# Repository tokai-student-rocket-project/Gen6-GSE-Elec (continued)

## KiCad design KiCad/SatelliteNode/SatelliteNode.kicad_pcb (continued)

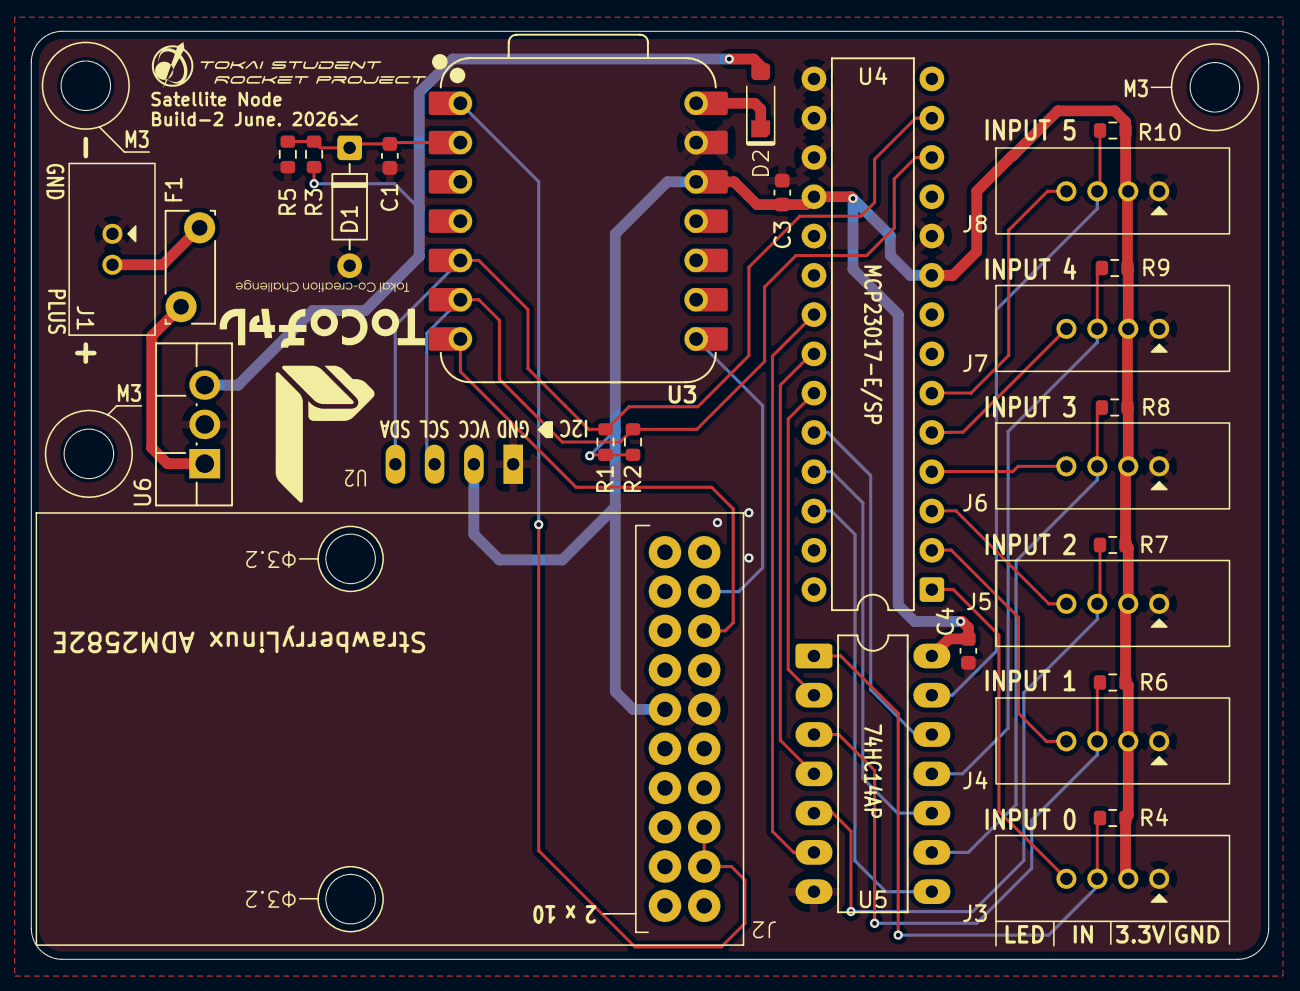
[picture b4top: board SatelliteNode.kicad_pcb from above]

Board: 2 copper layers, 80.0 x 60.0 mm, 32 parts (0 on the bottom side), 30 nets.

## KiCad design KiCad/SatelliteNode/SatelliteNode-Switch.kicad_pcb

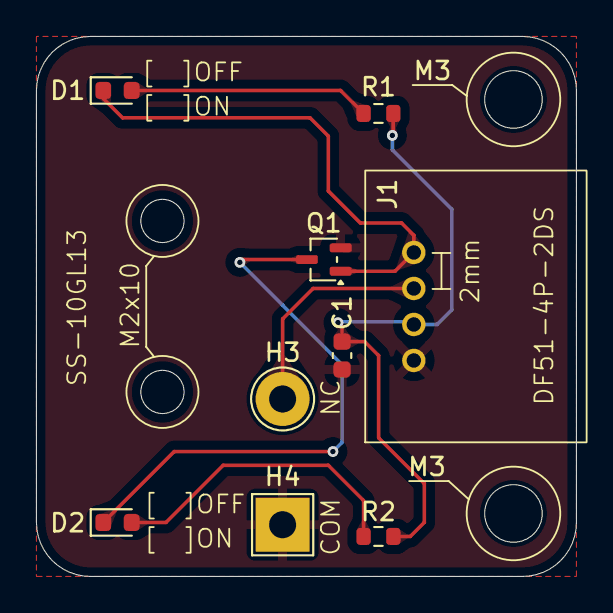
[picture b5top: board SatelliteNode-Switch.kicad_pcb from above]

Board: 2 copper layers, 30.0 x 30.0 mm, 11 parts (0 on the bottom side), 7 nets.

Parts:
C1: 0.1uF; C_0603_1608Metric
D1: GREEN; LED_0603_1608Metric
D2: RED; LED_0603_1608Metric
H3: MountingHole_Pad; TestPoint_THTPad_D3.0mm_Drill1.5mm
H4: MountingHole_Pad; TestPoint_THTPad_3.0x3.0mm_Drill1.5mm
J1: DF51A-4P-2DS
M3, M3#2: MountingHole; MountingHole_3.2mm_M3
Q1: DTC123EU3; SOT-323_SC-70
R1, R2: 330R; R_0603_1608Metric

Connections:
+3.3V: C1.1, J1.2, R1.1, R2.1
GND: C1.2, H4.1, J1.1, Q1.2 (E)
LED_CTRL: D1.1 (K), J1.4, Q1.1 (B)
unnamed: D1.2 (A), R1.2
unnamed: D2.2 (A), R2.2
unnamed: D2.1 (K), Q1.3 (C)
SW_OUT: H3.1, J1.3

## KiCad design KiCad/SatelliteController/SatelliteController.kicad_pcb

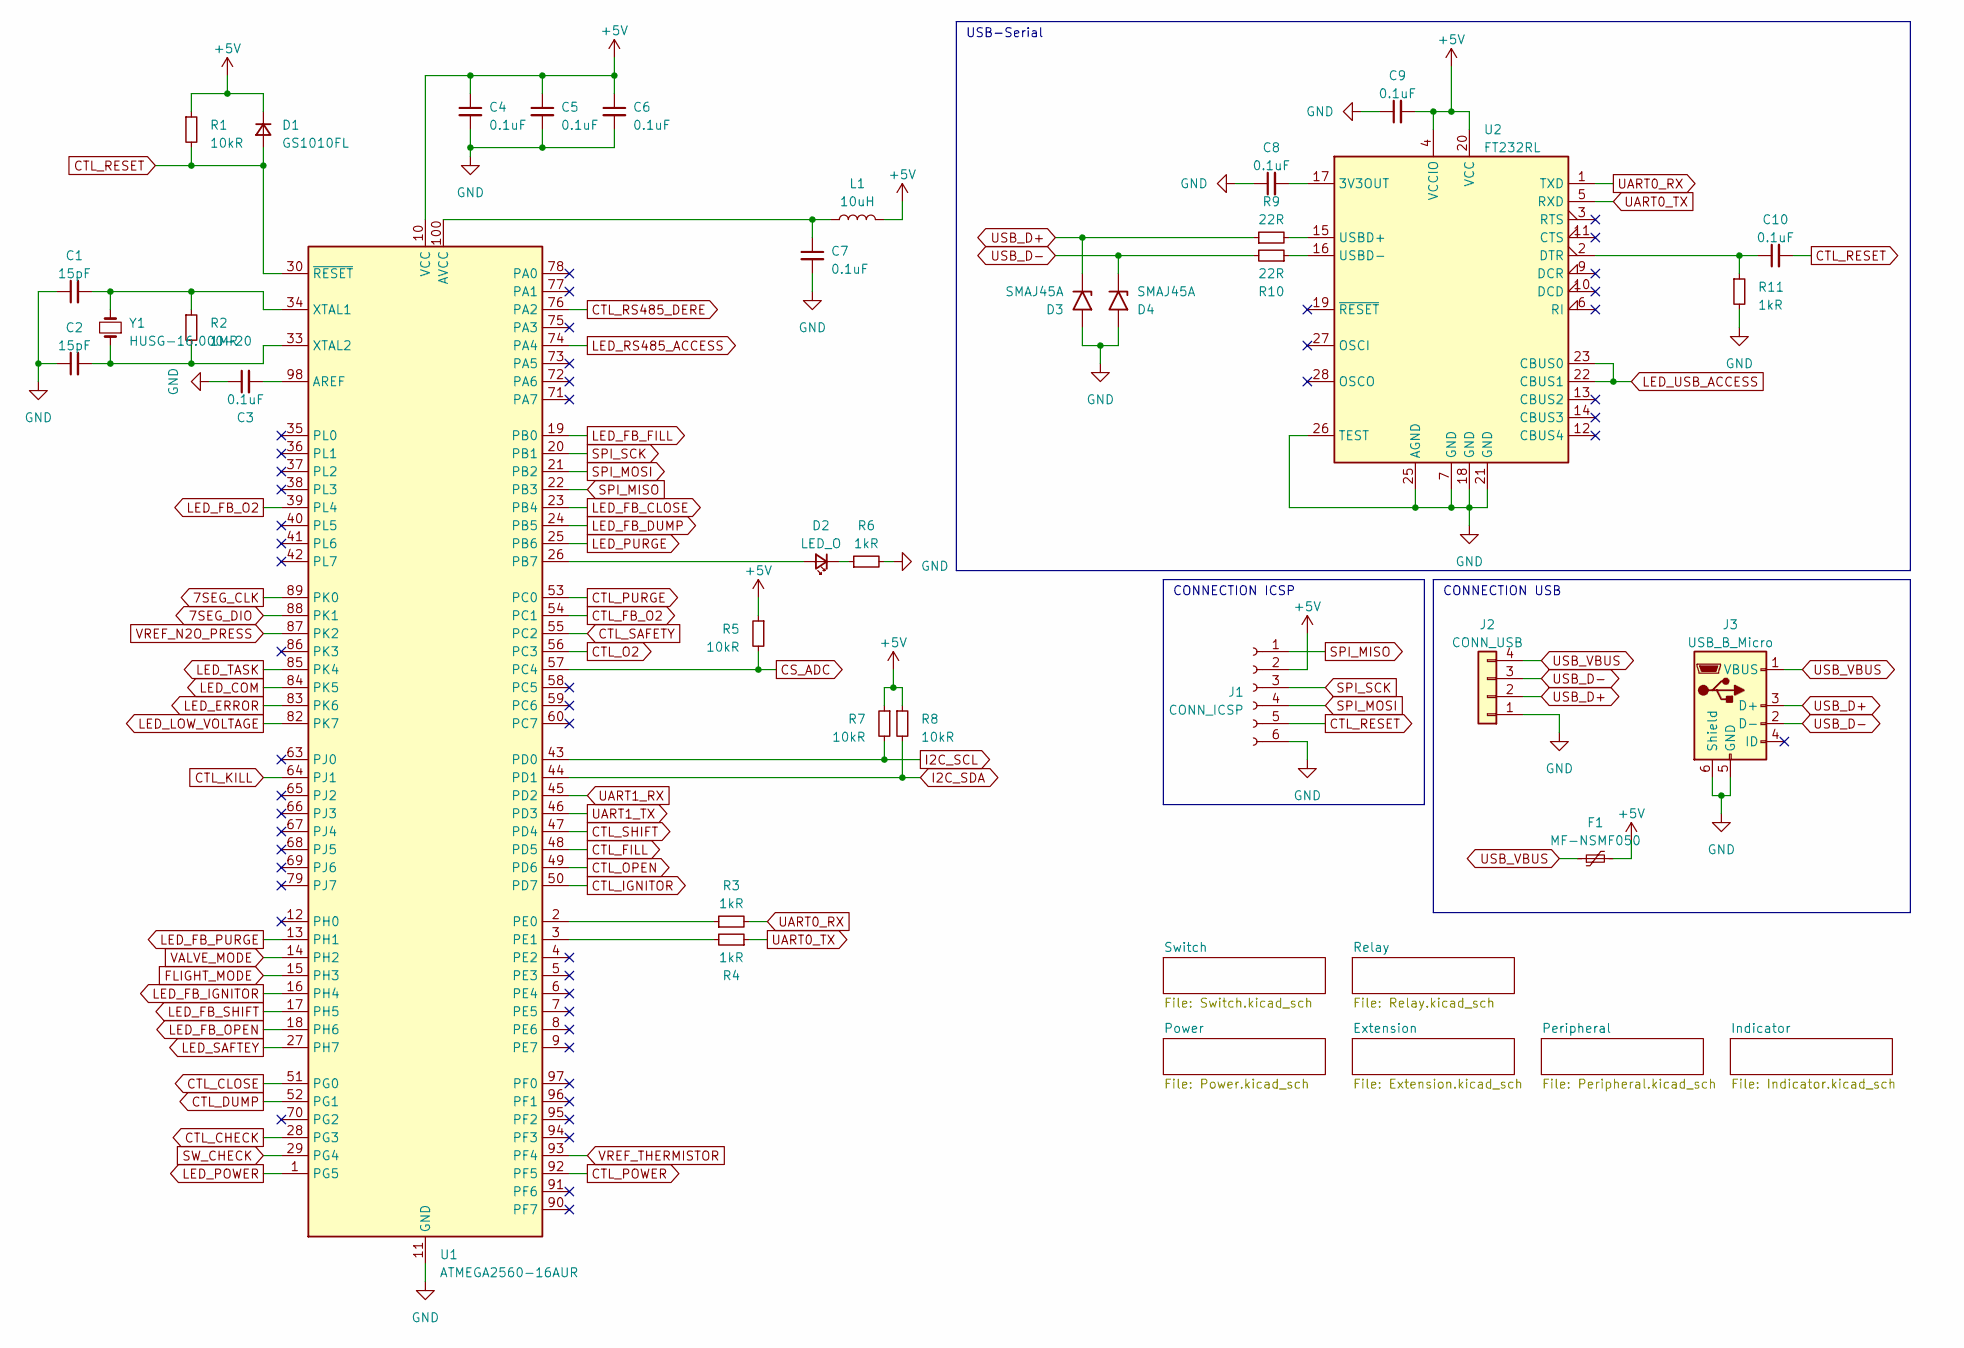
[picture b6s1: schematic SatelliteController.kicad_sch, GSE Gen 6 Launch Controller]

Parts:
C1, C2: 15pF; C_0603_1608Metric_Pad1.08x0.95mm_HandSolder
C3, C4, C5, C6, C7, C8, C9, C10: 0.1uF; C_0603_1608Metric_Pad1.08x0.95mm_HandSolder
D1: GS1010FL; D_SOD-123F
D2: LED_O; LED_0603_1608Metric_Pad1.05x0.95mm_HandSolder
D3, D4: SMAJ45A; D_SMA_Handsoldering
F1: MF-NSMF050; Fuse_1206_3216Metric_Pad1.42x1.75mm_HandSolder
J1: CONN_ICSP; PinSocket_1x06_P2.54mm_Vertical
J2: CONN_USB; TB401-1-4-E
J3: USB_B_Micro; USB_Micro-B_Wuerth_629105150521
L1: 10uH; L_1210_3225Metric_Pad1.42x2.65mm_HandSolder
R1, R5, R7, R8: 10kR; R_0603_1608Metric_Pad0.98x0.95mm_HandSolder
R2: 1MR; R_0603_1608Metric_Pad0.98x0.95mm_HandSolder
R3, R4, R6, R11: 1kR; R_0603_1608Metric_Pad0.98x0.95mm_HandSolder
R9, R10: 22R; R_0603_1608Metric_Pad0.98x0.95mm_HandSolder
U1: ATMEGA2560-16AUR; TQFP-100_14x14mm_P0.5mm
U2: FT232RL; SSOP-28_5.3x10.2mm_P0.65mm
Y1: HUSG-16.000-20; Crystal_HC49-U_Vertical

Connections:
7SEG_CLK: U1.89 (PK0); also elsewhere on the board
7SEG_DIO: U1.88 (PK1); also elsewhere on the board
CONN_LED_5V: C4.1, C5.1, C6.1, C9.2, D1.1 (K), F1.2, J1.2, L1.2, R1.1, R5.1, R7.1, R8.1, U1.10 (VCC), U1.31 (VCC), U1.61 (VCC), U1.80 (VCC), U2.4 (VCCIO), U2.20 (VCC); also elsewhere on the board
CONN_LED_CHECK: U1.28 (PG3); also elsewhere on the board
CONN_LED_COM: U1.84 (PK5); also elsewhere on the board
CONN_LED_ERROR: U1.83 (PK6); also elsewhere on the board
CONN_LED_LOW_VOLTAGE: U1.82 (PK7); also elsewhere on the board
CONN_LED_RS485_ACCESS: U1.74 (PA4); also elsewhere on the board
CONN_LED_SAFTEY: U1.27 (PH7); also elsewhere on the board
CONN_LED_TASK: U1.85 (PK4); also elsewhere on the board
CONN_LED_USB_ACCESS: U2.22 (CBUS1), U2.23 (CBUS0); also elsewhere on the board
CS_ADC: R5.2, U1.57 (PC4); also elsewhere on the board
CTL_CLOSE: U1.51 (PG0); also elsewhere on the board
CTL_DUMP: U1.52 (PG1); also elsewhere on the board
CTL_FB_O2: U1.54 (PC1)
CTL_FILL: U1.48 (PD5); also elsewhere on the board
CTL_IGNITOR: U1.50 (PD7); also elsewhere on the board
CTL_KILL: U1.64 (PJ1); also elsewhere on the board
CTL_O2: U1.56 (PC3); also elsewhere on the board
CTL_OPEN: U1.49 (PD6); also elsewhere on the board
CTL_POWER: U1.92 (PF5); also elsewhere on the board
CTL_PURGE: U1.53 (PC0); also elsewhere on the board
CTL_RESET: C10.2, D1.2 (A), J1.5, R1.2, U1.30 (~RESET); also elsewhere on the board
CTL_RS485_DERE: U1.76 (PA2); also elsewhere on the board
CTL_SAFETY: U1.55 (PC2); also elsewhere on the board
CTL_SHIFT: U1.47 (PD4); also elsewhere on the board
FLIGHT_MODE: U1.15 (PH3); also elsewhere on the board
GND: C1.1, C2.1, C3.1, C4.2, C5.2, C6.2, C7.2, C8.1, C9.1, D3.2 (A2), D4.2 (A2), J1.6, J2.1, J3.5 (GND), J3.6 (Shield), R6.2, R11.2, U1.11 (GND), U1.32 (GND), U1.62 (GND), U1.81 (GND), U1.99 (GND), U2.7 (GND), U2.18 (GND), U2.21 (GND), U2.25 (AGND), U2.26 (TEST); also elsewhere on the board
I2C_SCL: R7.2, U1.43 (PD0); also elsewhere on the board
I2C_SDA: R8.2, U1.44 (PD1); also elsewhere on the board
LED_PURGE: U1.25 (PB6)
unnamed: D2.2 (A), U1.26 (PB7)
unnamed: D2.1 (K), R6.1
unnamed: C3.2, U1.98 (AREF)
unnamed: C7.1, L1.1, U1.100 (AVCC)
unnamed: R3.1, U1.2 (PE0)
unnamed: R4.2, U1.3 (PE1)
unnamed: C1.2, R2.1, U1.34 (XTAL1), Y1.2
unnamed: C2.2, R2.2, U1.33 (XTAL2), Y1.1
unnamed: C8.2, U2.17 (3V3OUT)
unnamed: C10.1, R11.1, U2.2 (DTR)
unnamed: R9.2, U2.15 (USBD+)
unnamed: R10.1, U2.16 (USBD-)
SPI_MISO: J1.1, U1.22 (PB3); also elsewhere on the board
SPI_MOSI: J1.4, U1.21 (PB2); also elsewhere on the board
SPI_SCK: J1.3, U1.20 (PB1); also elsewhere on the board
SW_CHECK: U1.29 (PG4); also elsewhere on the board
UART0_RX: R3.2, U2.1 (TXD)
UART0_TX: R4.1, U2.5 (RXD)
UART1_RX: U1.45 (PD2); also elsewhere on the board
UART1_TX: U1.46 (PD3); also elsewhere on the board
USB_D+: D3.1 (A1), J2.2, J3.3 (D+), R9.1
USB_D-: D4.1 (A1), J2.3, J3.2 (D-), R10.2
USB_VBUS: F1.1, J2.4, J3.1 (VBUS)
VALVE_MODE: U1.14 (PH2); also elsewhere on the board
VREF_N2O_PRESS: U1.87 (PK2); also elsewhere on the board
VREF_THERMISTOR: U1.93 (PF4); also elsewhere on the board

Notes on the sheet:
CONNECTION ICSP
CONNECTION USB
USB-Serial

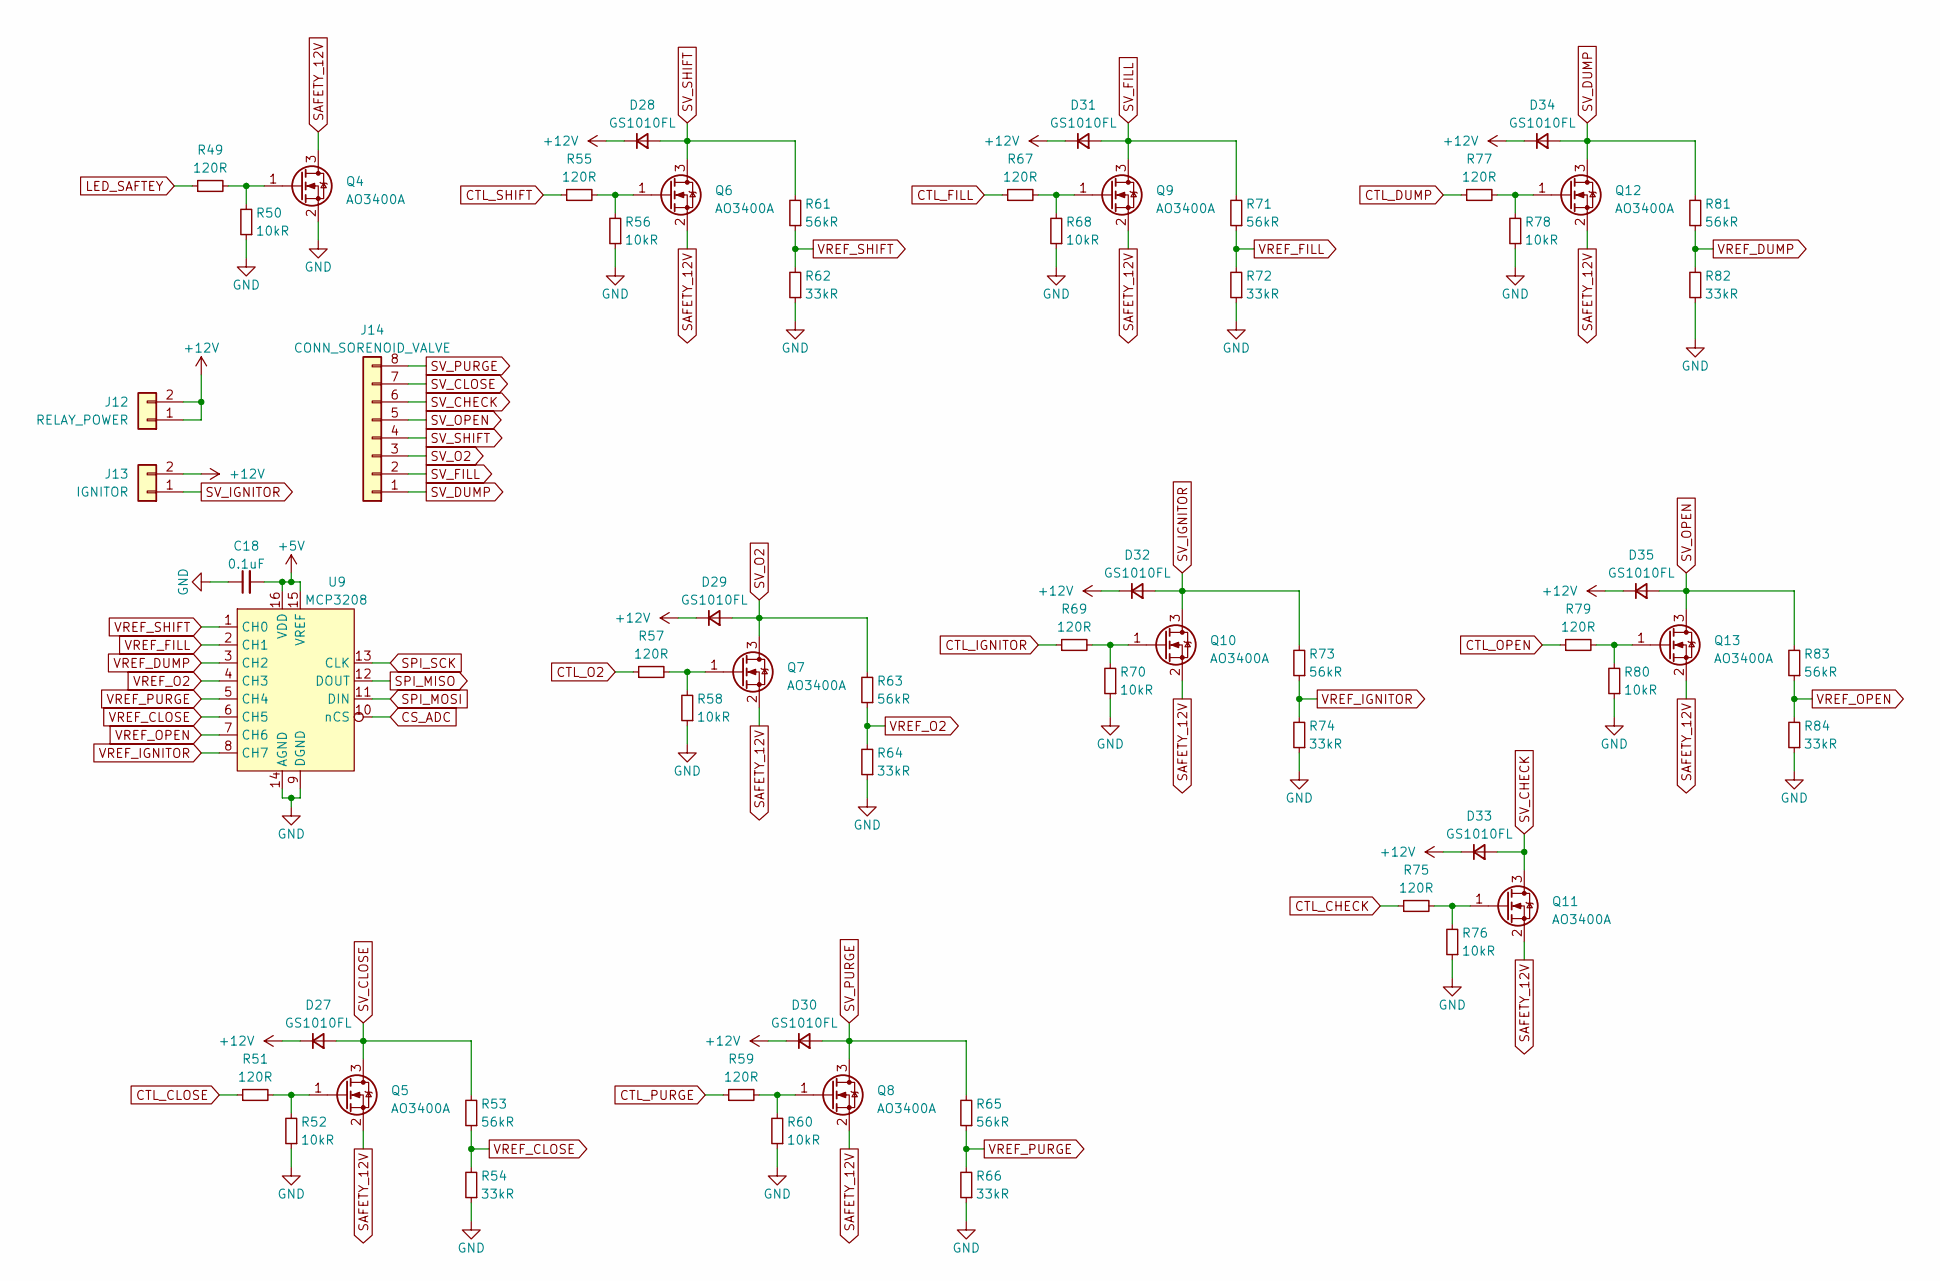
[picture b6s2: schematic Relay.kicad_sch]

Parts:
C18: 0.1uF; C_0603_1608Metric_Pad1.08x0.95mm_HandSolder
D27, D28, D29, D30, D31, D32, D33, D34, D35: GS1010FL; D_SOD-123F
J12: RELAY_POWER; TB411-2-2-E-1
J13: IGNITOR; TB411-2-2-E-1
J14: CONN_SORENOID_VALVE; DF51A-8DP-2DS
Q4, Q5, Q6, Q7, Q8, Q9, Q10, Q11, Q12, Q13: AO3400A; SOT-23
R49, R51, R55, R57, R59, R67, R69, R75, R77, R79: 120R; R_0603_1608Metric_Pad0.98x0.95mm_HandSolder
R50, R52, R56, R58, R60, R68, R70, R76, R78, R80: 10kR; R_0603_1608Metric_Pad0.98x0.95mm_HandSolder
R53, R61, R63, R65, R71, R73, R81, R83: 56kR; R_0603_1608Metric_Pad0.98x0.95mm_HandSolder
R54, R62, R64, R66, R72, R74, R82, R84: 33kR; R_0603_1608Metric_Pad0.98x0.95mm_HandSolder
U9: MCP3208; DIP-16_W7.62mm

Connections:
CONN_LED_5V: C18.2, U9.15 (VREF), U9.16 (VDD); also elsewhere on the board
CONN_LED_12V: D27.1 (K), D28.1 (K), D29.1 (K), D30.1 (K), D31.1 (K), D32.1 (K), D33.1 (K), D34.1 (K), D35.1 (K), J12.1, J12.2, J13.2; also elsewhere on the board
CONN_LED_CHECK: R75.1; also elsewhere on the board
CONN_LED_SAFTEY: R49.1; also elsewhere on the board
CS_ADC: U9.10 (nCS); also elsewhere on the board
CTL_CLOSE: R51.1; also elsewhere on the board
CTL_DUMP: R77.1; also elsewhere on the board
CTL_FILL: R67.1; also elsewhere on the board
CTL_IGNITOR: R69.1; also elsewhere on the board
CTL_O2: R57.1; also elsewhere on the board
CTL_OPEN: R79.1; also elsewhere on the board
CTL_PURGE: R59.1; also elsewhere on the board
CTL_SHIFT: R55.1; also elsewhere on the board
GND: C18.1, Q4.2 (S), R50.1, R52.1, R54.1, R56.1, R58.1, R60.1, R62.1, R64.1, R66.1, R68.1, R70.1, R72.1, R74.1, R76.1, R78.1, R80.1, R82.1, R84.1, U9.9 (DGND), U9.14 (AGND); also elsewhere on the board
unnamed: Q4.1 (G), R49.2, R50.2
unnamed: Q5.1 (G), R51.2, R52.2
unnamed: Q6.1 (G), R55.2, R56.2
unnamed: Q7.1 (G), R57.2, R58.2
unnamed: Q8.1 (G), R59.2, R60.2
unnamed: Q9.1 (G), R67.2, R68.2
unnamed: Q10.1 (G), R69.2, R70.2
unnamed: Q11.1 (G), R75.2, R76.2
unnamed: Q12.1 (G), R77.2, R78.2
unnamed: Q13.1 (G), R79.2, R80.2
SAFETY_12V: Q4.3 (D), Q5.2 (S), Q6.2 (S), Q7.2 (S), Q8.2 (S), Q9.2 (S), Q10.2 (S), Q11.2 (S), Q12.2 (S), Q13.2 (S)
SPI_MISO: U9.12 (DOUT); also elsewhere on the board
SPI_MOSI: U9.11 (DIN); also elsewhere on the board
SPI_SCK: U9.13 (CLK); also elsewhere on the board
SV_CHECK: D33.2 (A), J14.6, Q11.3 (D)
SV_CLOSE: D27.2 (A), J14.7, Q5.3 (D), R53.2
SV_DUMP: D34.2 (A), J14.1, Q12.3 (D), R81.2
SV_FILL: D31.2 (A), J14.2, Q9.3 (D), R71.2
SV_IGNITOR: D32.2 (A), J13.1, Q10.3 (D), R73.2
SV_O2: D29.2 (A), J14.3, Q7.3 (D), R63.2
SV_OPEN: D35.2 (A), J14.5, Q13.3 (D), R83.2
SV_PURGE: D30.2 (A), J14.8, Q8.3 (D), R65.2
SV_SHIFT: D28.2 (A), J14.4, Q6.3 (D), R61.2
VREF_CLOSE: R53.1, R54.2, U9.6 (CH5)
VREF_DUMP: R81.1, R82.2, U9.3 (CH2)
VREF_FILL: R71.1, R72.2, U9.2 (CH1)
VREF_IGNITOR: R73.1, R74.2, U9.8 (CH7)
VREF_O2: R63.1, R64.2, U9.4 (CH3)
VREF_OPEN: R83.1, R84.2, U9.7 (CH6)
VREF_PURGE: R65.1, R66.2, U9.5 (CH4)
VREF_SHIFT: R61.1, R62.2, U9.1 (CH0)

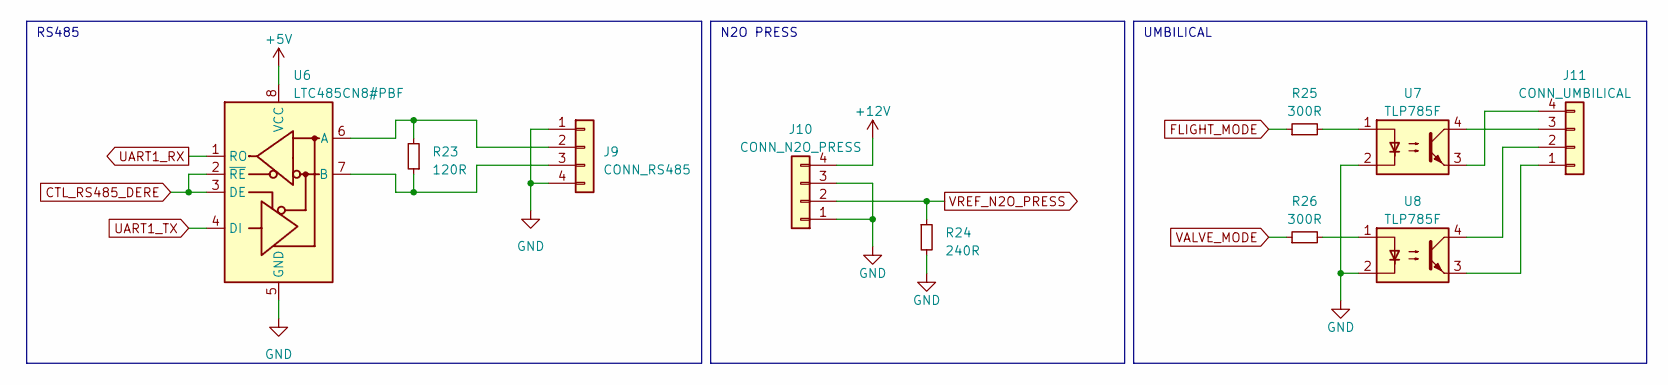
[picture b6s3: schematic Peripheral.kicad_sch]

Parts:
J9: CONN_RS485; TB401-1-4-E
J10: CONN_N2O_PRESS; TB401-1-4-E
J11: CONN_UMBILICAL; TB401-1-4-E
R23: 120R; R_0603_1608Metric_Pad0.98x0.95mm_HandSolder
R24: 240R; R_0603_1608Metric_Pad0.98x0.95mm_HandSolder
R25, R26: 300R; R_0603_1608Metric_Pad0.98x0.95mm_HandSolder
U6: LTC485CN8#PBF; DIP-8_W7.62mm
U7, U8: TLP785F; DIP-4_W10.16mm

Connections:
CONN_LED_5V: U6.8 (VCC); also elsewhere on the board
CONN_LED_12V: J10.4; also elsewhere on the board
CTL_RS485_DERE: U6.2 (~RE), U6.3 (DE); also elsewhere on the board
FLIGHT_MODE: R25.1; also elsewhere on the board
GND: J9.1, J9.4, J10.1, J10.3, R24.2, U6.5 (GND), U7.2, U8.2; also elsewhere on the board
unnamed: J9.2, R23.2, U6.6 (A)
unnamed: J9.3, R23.1, U6.7 (B)
unnamed: J11.1, U8.3
unnamed: J11.2, U8.4
unnamed: J11.3, U7.4
unnamed: J11.4, U7.3
unnamed: R25.2, U7.1
unnamed: R26.2, U8.1
UART1_RX: U6.1 (RO); also elsewhere on the board
UART1_TX: U6.4 (DI); also elsewhere on the board
VALVE_MODE: R26.1; also elsewhere on the board
VREF_N2O_PRESS: J10.2, R24.1; also elsewhere on the board

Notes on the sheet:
N2O PRESS
UMBILICAL
RS485

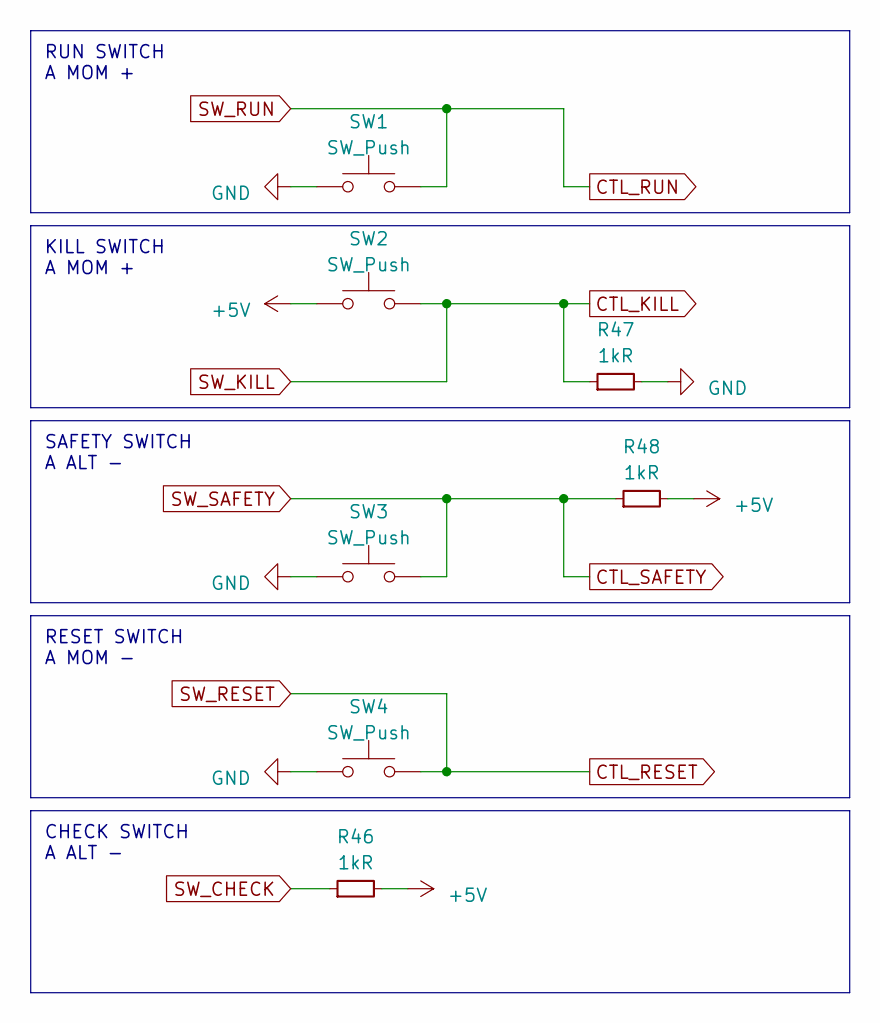
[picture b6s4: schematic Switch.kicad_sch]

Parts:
R46, R47, R48: 1kR; R_0603_1608Metric_Pad0.98x0.95mm_HandSolder
SW1, SW2, SW4: SW_Push; TVAF06-A020B-R
SW3: SW_Push; PinHeader_1x02_P2.54mm_Vertical

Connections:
CONN_LED_5V: R46.2, R48.2, SW2.1; also elsewhere on the board
CTL_KILL: R47.1, SW2.2; also elsewhere on the board
CTL_RESET: SW4.2; also elsewhere on the board
CTL_RUN: SW1.2; also elsewhere on the board
CTL_SAFETY: R48.1, SW3.2; also elsewhere on the board
GND: R47.2, SW1.1, SW3.1, SW4.1; also elsewhere on the board
SW_CHECK: R46.1; also elsewhere on the board

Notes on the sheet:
KILL SWITCH A MOM +
SAFETY SWITCH A ALT -
CHECK SWITCH A ALT -
RESET SWITCH A MOM -
RUN SWITCH A MOM +

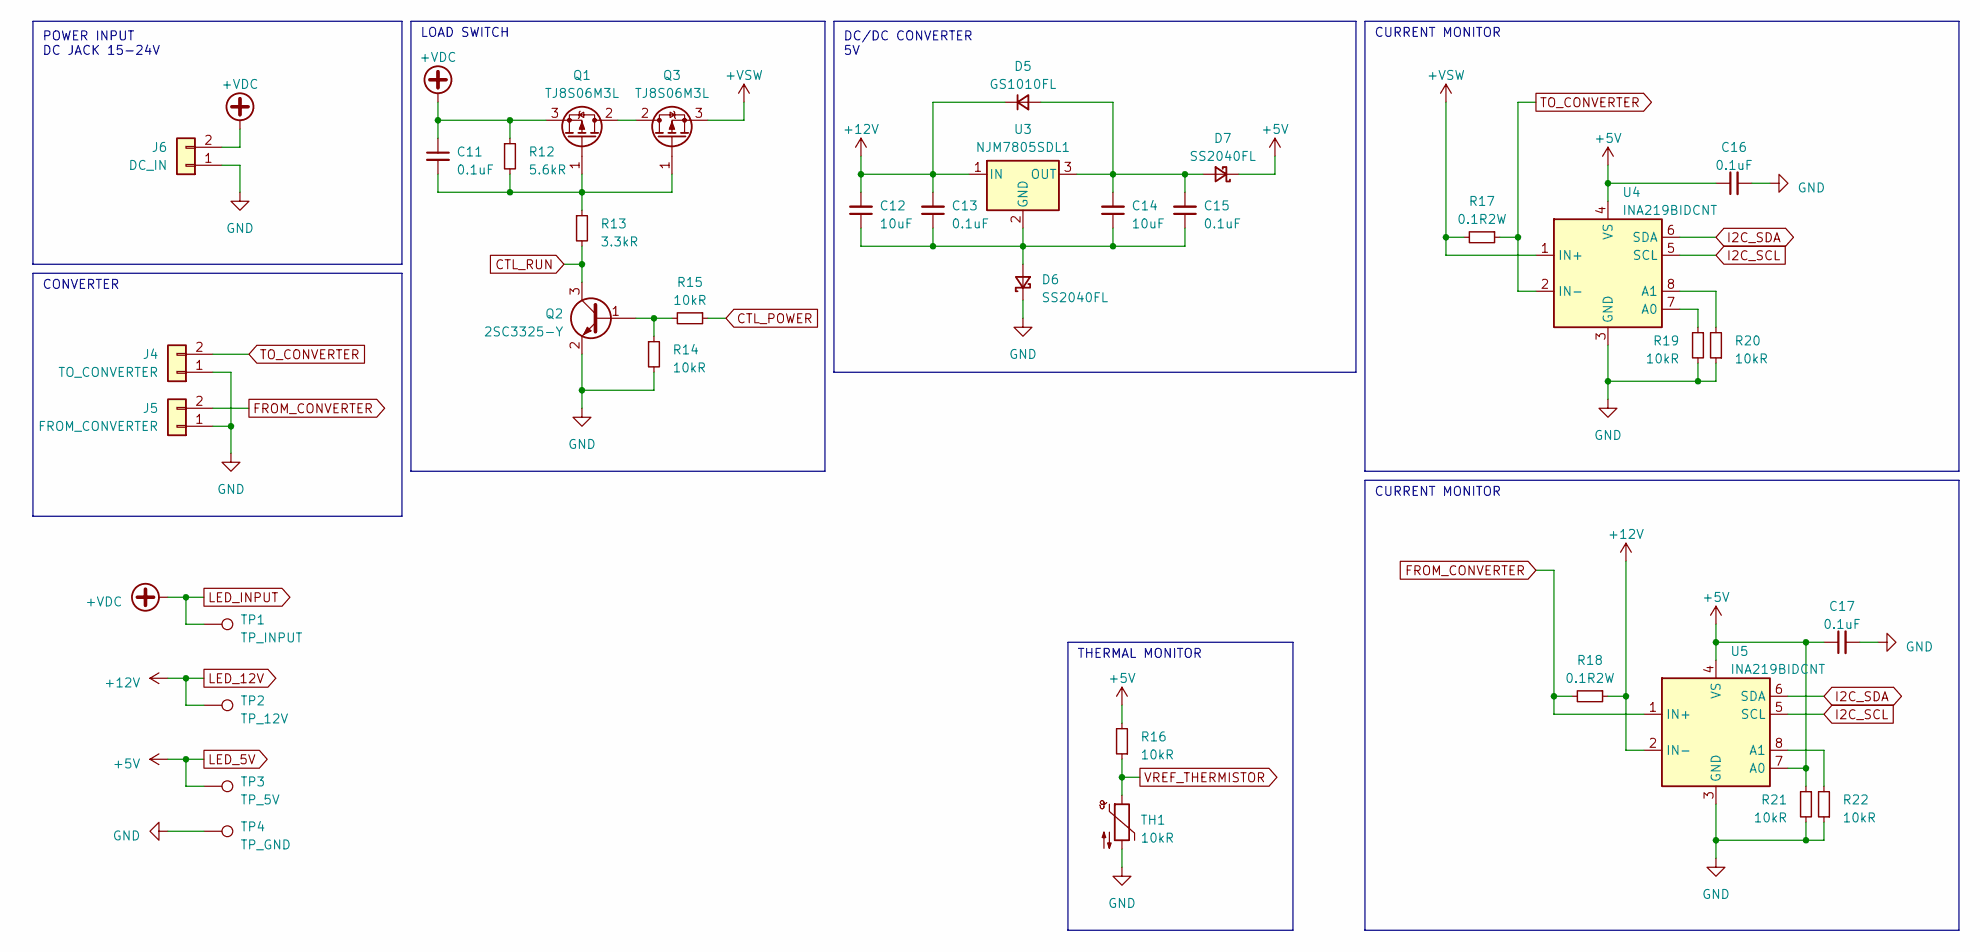
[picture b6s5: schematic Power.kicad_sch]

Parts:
C11, C13, C15, C16, C17: 0.1uF; C_0603_1608Metric_Pad1.08x0.95mm_HandSolder
C12, C14: 10uF; C_1206_3216Metric_Pad1.33x1.80mm_HandSolder
D5: GS1010FL; D_SOD-123F
D6, D7: SS2040FL; D_SOD-123F
J4: TO_CONVERTER; TB411-2-2-E-1
J5: FROM_CONVERTER; TB411-2-2-E-1
J6: DC_IN; TB411-2-2-E-1
Q1, Q3: TJ8S06M3L; TO-252-2
Q2: 2SC3325-Y; SC-59_Handsoldering
R12: 5.6kR; R_0603_1608Metric_Pad0.98x0.95mm_HandSolder
R13: 3.3kR; R_0603_1608Metric_Pad0.98x0.95mm_HandSolder
R14, R15, R16, R19, R20, R21, R22: 10kR; R_0603_1608Metric_Pad0.98x0.95mm_HandSolder
R17, R18: 0.1R2W; R_2816_7142Metric_Pad3.20x4.45mm_HandSolder
TH1: 10kR; R_0603_1608Metric_Pad0.98x0.95mm_HandSolder
TP1: TP_INPUT; TestPoint_THTPad_D2.5mm_Drill1.2mm
TP2: TP_12V; TestPoint_THTPad_D2.5mm_Drill1.2mm
TP3: TP_5V; TestPoint_THTPad_D2.5mm_Drill1.2mm
TP4: TP_GND; TestPoint_THTPad_D2.5mm_Drill1.2mm
U3: NJM7805SDL1; TO-252-2
U4, U5: INA219BIDCNT; SOT-23-8

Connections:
+VSW: Q3.3 (S), R17.2, U4.1 (IN+)
CONN_LED_5V: C16.1, C17.1, D7.1 (K), R16.2, R21.1, TP3.1, U4.4 (VS), U5.4 (VS), U5.7 (A0); also elsewhere on the board
CONN_LED_12V: C12.2, C13.2, D5.1 (K), R18.1, TP2.1, U3.1 (IN), U5.2 (IN-); also elsewhere on the board
CONN_LED_INPUT: C11.1, J6.2, Q1.3 (S), R12.1, TP1.1; also elsewhere on the board
CTL_POWER: R15.1; also elsewhere on the board
CTL_RUN: Q2.3 (C), R13.2; also elsewhere on the board
FROM_CONVERTER: J5.2, R18.2, U5.1 (IN+)
GND: C16.2, C17.2, D6.1 (K), J4.1, J5.1, J6.1, Q2.2 (E), R14.2, R19.2, R20.1, R21.2, R22.1, TH1.2, TP4.1, U4.3 (GND), U5.3 (GND); also elsewhere on the board
I2C_SCL: U4.5 (SCL), U5.5 (SCL); also elsewhere on the board
I2C_SDA: U4.6 (SDA), U5.6 (SDA); also elsewhere on the board
unnamed: C14.2, C15.2, D5.2 (A), D7.2 (A), U3.3 (OUT)
unnamed: C12.1, C13.1, C14.1, C15.1, D6.2 (A), U3.2 (GND)
unnamed: Q1.2 (D), Q3.2 (D)
unnamed: C11.2, Q1.1 (G), Q3.1 (G), R12.2, R13.1
unnamed: Q2.1 (B), R14.1, R15.2
unnamed: R19.1, U4.7 (A0)
unnamed: R20.2, U4.8 (A1)
unnamed: R22.2, U5.8 (A1)
TO_CONVERTER: J4.2, R17.1, U4.2 (IN-)
VREF_THERMISTOR: R16.1, TH1.1; also elsewhere on the board

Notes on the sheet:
CURRENT MONITOR
POWER INPUT DC JACK 15-24V
DC/DC CONVERTER 5V
CONVERTER
THERMAL MONITOR
LOAD SWITCH

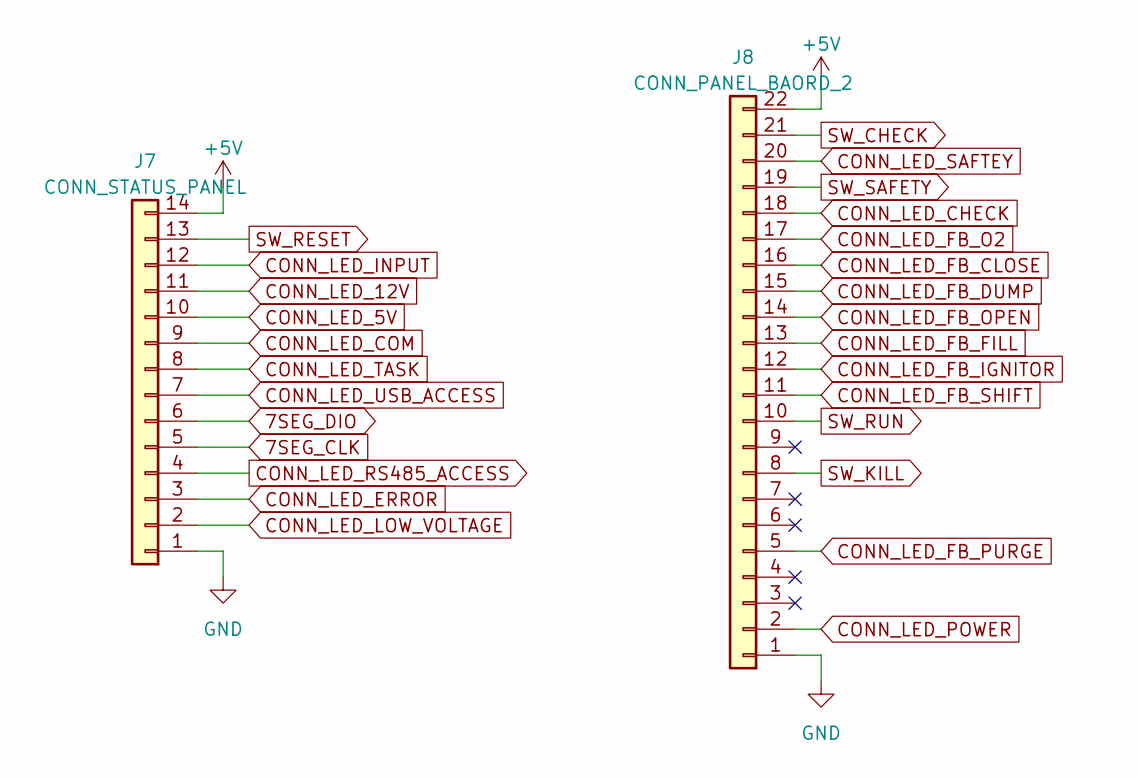
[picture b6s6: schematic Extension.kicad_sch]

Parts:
J7: CONN_STATUS_PANEL; DF51A-14DP-2DS
J8: CONN_PANEL_BAORD_2; DF51A-22DP-2DS

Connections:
7SEG_CLK: J7.5; also elsewhere on the board
7SEG_DIO: J7.6; also elsewhere on the board
CONN_LED_5V: J7.10, J7.14, J8.22; also elsewhere on the board
CONN_LED_12V: J7.11; also elsewhere on the board
CONN_LED_CHECK: J8.18; also elsewhere on the board
CONN_LED_COM: J7.9; also elsewhere on the board
CONN_LED_ERROR: J7.3; also elsewhere on the board
CONN_LED_INPUT: J7.12; also elsewhere on the board
CONN_LED_LOW_VOLTAGE: J7.2; also elsewhere on the board
CONN_LED_RS485_ACCESS: J7.4; also elsewhere on the board
CONN_LED_SAFTEY: J8.20; also elsewhere on the board
CONN_LED_TASK: J7.8; also elsewhere on the board
CONN_LED_USB_ACCESS: J7.7; also elsewhere on the board
CTL_KILL: J8.8; also elsewhere on the board
CTL_RESET: J7.13; also elsewhere on the board
CTL_RUN: J8.10; also elsewhere on the board
CTL_SAFETY: J8.19; also elsewhere on the board
GND: J7.1, J8.1; also elsewhere on the board
SW_CHECK: J8.21; also elsewhere on the board

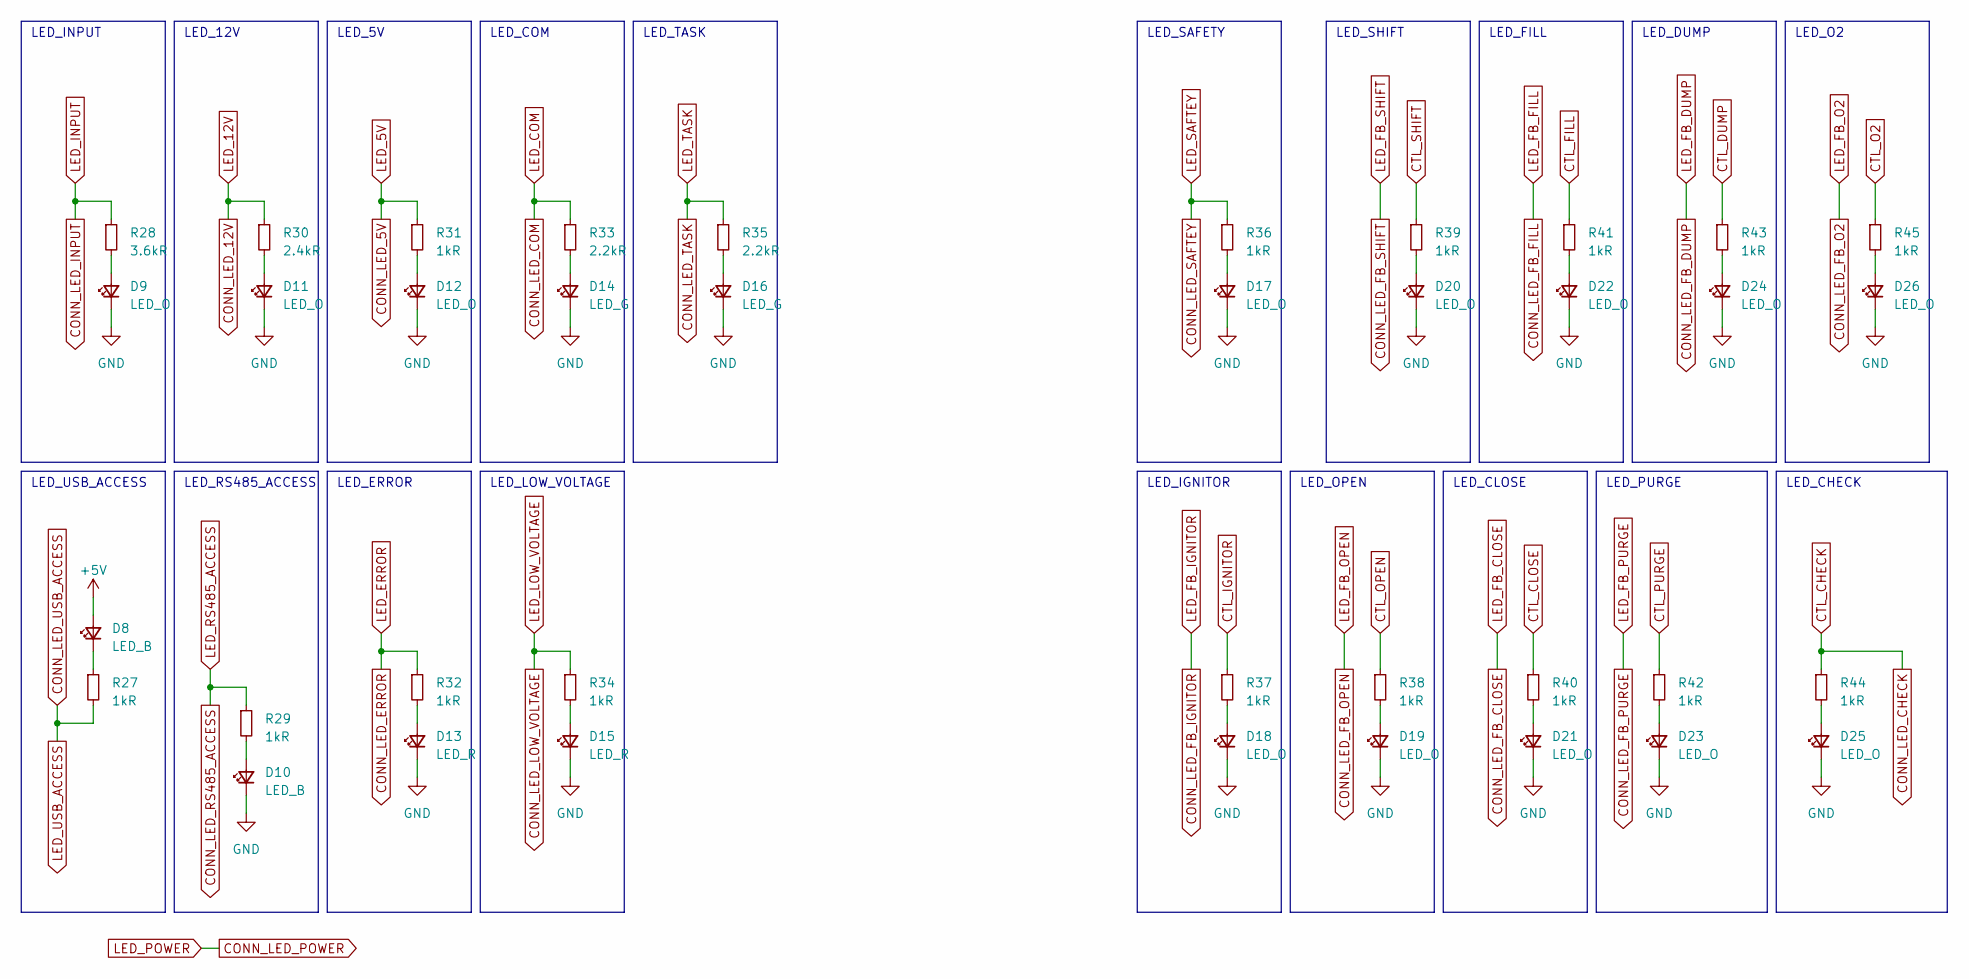
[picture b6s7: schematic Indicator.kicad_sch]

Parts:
D8, D10: LED_B; LED_0603_1608Metric_Pad1.05x0.95mm_HandSolder
D9, D11, D12, D17, D18, D19, D20, D21, D22, D23, D24, D25, D26: LED_O; LED_0603_1608Metric_Pad1.05x0.95mm_HandSolder
D13, D15: LED_R; LED_0603_1608Metric_Pad1.05x0.95mm_HandSolder
D14, D16: LED_G; LED_0603_1608Metric_Pad1.05x0.95mm_HandSolder
R27, R29, R31, R32, R34, R36, R37, R38, R39, R40, R41, R42, R43, R44, R45: 1kR; R_0603_1608Metric_Pad0.98x0.95mm_HandSolder
R28: 3.6kR; R_0603_1608Metric_Pad0.98x0.95mm_HandSolder
R30: 2.4kR; R_0603_1608Metric_Pad0.98x0.95mm_HandSolder
R33, R35: 2.2kR; R_0603_1608Metric_Pad0.98x0.95mm_HandSolder

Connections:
CONN_LED_5V: D8.2 (A), R31.1; also elsewhere on the board
CONN_LED_12V: R30.1; also elsewhere on the board
CONN_LED_CHECK: R44.1; also elsewhere on the board
CONN_LED_COM: R33.1; also elsewhere on the board
CONN_LED_ERROR: R32.1; also elsewhere on the board
CONN_LED_INPUT: R28.1; also elsewhere on the board
CONN_LED_LOW_VOLTAGE: R34.1; also elsewhere on the board
CONN_LED_RS485_ACCESS: R29.1; also elsewhere on the board
CONN_LED_SAFTEY: R36.1; also elsewhere on the board
CONN_LED_TASK: R35.1; also elsewhere on the board
CONN_LED_USB_ACCESS: R27.2; also elsewhere on the board
CTL_CLOSE: R40.1; also elsewhere on the board
CTL_DUMP: R43.1; also elsewhere on the board
CTL_FILL: R41.1; also elsewhere on the board
CTL_IGNITOR: R37.1; also elsewhere on the board
CTL_O2: R45.1; also elsewhere on the board
CTL_OPEN: R38.1; also elsewhere on the board
CTL_PURGE: R42.1; also elsewhere on the board
CTL_SHIFT: R39.1; also elsewhere on the board
GND: D9.1 (K), D10.1 (K), D11.1 (K), D12.1 (K), D13.1 (K), D14.1 (K), D15.1 (K), D16.1 (K), D17.1 (K), D18.1 (K), D19.1 (K), D20.1 (K), D21.1 (K), D22.1 (K), D23.1 (K), D24.1 (K), D25.1 (K), D26.1 (K); also elsewhere on the board
unnamed: D8.1 (K), R27.1
unnamed: D9.2 (A), R28.2
unnamed: D10.2 (A), R29.2
unnamed: D11.2 (A), R30.2
unnamed: D12.2 (A), R31.2
unnamed: D13.2 (A), R32.2
unnamed: D14.2 (A), R33.2
unnamed: D15.2 (A), R34.2
unnamed: D16.2 (A), R35.2
unnamed: D17.2 (A), R36.2
unnamed: D18.2 (A), R37.2
unnamed: D19.2 (A), R38.2
unnamed: D20.2 (A), R39.2
unnamed: D21.2 (A), R40.2
unnamed: D22.2 (A), R41.2
unnamed: D23.2 (A), R42.2
unnamed: D24.2 (A), R43.2
unnamed: D25.2 (A), R44.2
unnamed: D26.2 (A), R45.2

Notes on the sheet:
LED_CLOSE
LED_ERROR
LED_RS485_ACCESS
LED_DUMP
LED_TASK
LED_PURGE
LED_FILL
LED_LOW_VOLTAGE
LED_O2
LED_COM
LED_5V
LED_SHIFT
LED_USB_ACCESS
LED_IGNITOR
LED_OPEN
LED_INPUT
LED_SAFETY
LED_12V
LED_CHECK

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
